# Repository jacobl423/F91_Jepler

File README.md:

# F91_Jepler

## Project Overview

The **F91_Jepler** is a complete redesign and evolution of the classic Casio F91W watch, inspired by the original [F91 Kepler](https://github.com/drpykachu/F91_Kepler) project. This project completely replaces the original internals of the watch, keeping only the original resin case and buttons, while adding an OLED display, a powerful Bluetooth-capable MCU, and a rechargeable battery system.

The redesign is in progress. Emulation, tooling and companion software are far along; the nRF52840 board itself is not fabricated, and fit and charging arrangements are not yet verified.

## Progress at a Glance

| Area | Status |
|---|---|
| **Hardware** | Original Kepler DipTrace PCBs converted to editable KiCad 10 projects; redesign draft board carried in the workbench app; BOMs and clock requirements documented. Nothing fabricated yet. |
| **Firmware** | Zephyr RTOS app boots under MCUboot in Renode: RTC-backed ticking clock, SSD1306 framebuffer over I2C, and the custom Notification and Clock GATT services ported to the Zephyr BLE stack. |
| **Emulation** | One-command firmware build with SHA-256 manifest, signed-image boot verification, browser watch viewer with real emulated framebuffer and GPIO buttons, headless boot check. |
| **Jepler Dev (macOS)** | Full Swift workbench: Renode session harness, UART terminal, watch face, firmware build/verify, automated test runner, UART test-bridge injectors, and a live KiCad suite (auto-reload viewer, 3D raytrace, DRC, Gerber export, diff). |
| **Companion app** | React + Capacitor mobile app (Android/iOS) with BLE scan/connect, GATT clock sync, mock driver and LCD watch face; **327/327 tests passing** (`npm test` in `Software/companion_app`). |

## Hardware Upgrades & Architecture

The original Kepler boards were authored in DipTrace; those files are retained unchanged in [`Hardware/PCB/`](Hardware/PCB) and have been converted into editable KiCad projects in [`Hardware/KiCad/`](Hardware/KiCad) (main board, display connector, debugger connector).

The nRF52840 redesign draft (A0) previously lived under `Hardware/KiCad/drafts/f91_jepler/`; that standalone copy was removed when the original boards were converted, and the same draft PCB now ships inside the workbench app at [`Software/macOS_App/F91JeplerEmulator/Resources/Embedded/f91_jepler.kicad_pcb`](Software/macOS_App/F91JeplerEmulator/Resources/Embedded/f91_jepler.kicad_pcb), where the Jepler Dev PCB tools open it by default. It remains an **unrouted electrical-core and placement draft, not a fabrication release**.

- **MCU:** Nordic nRF52840-QIAA, 7 × 7 mm AQFN73, with 1 MB flash and 256 KB RAM.
- **Display:** BuyDisplay ER-OLED0.83-1, a 0.83″ 96 × 39 monochrome OLED driven over I2C (SSD1306-class, Zephyr CFB framebuffer). Connector and supply details remain provisional.
- **Battery:** A small protected single-cell LiPo secured to the assembly replaces the earlier rechargeable coin-cell plan. Exact cell and fit remain provisional.
- **Power:** The draft includes a 3.0 V regulator (not a charger). Onboard charging, charge/load management and the charging connector still need design work.
- **Timekeeping:** External 32.768 kHz crystal feeding the nRF52840 RTC; see [clock circuit requirements](Hardware/CLOCKING.md).
- **Sensors:** An accelerometer and external flash remain optional; neither is in the draft.

### Bracket and charging contacts

Retain the original bracket as the mechanical reference. Its continuity, spring geometry, insulation and clearance around a new battery have not been measured. The user does not currently have it available, so those aspects remain provisional. The draft does not connect the bracket to a battery or charging net. Earlier split-cage and button-charging ideas in the historical project context are not approved electrical designs.

## Software Architecture

Moving to the nRF52840 means the original Texas Instruments SimpleLink firmware is being completely replaced. The new firmware is built on:
- **Zephyr RTOS / nRF Connect SDK:** The modern standard for Nordic BLE development.
- **MCUboot + SMP Server:** MCUboot is the first-stage bootloader with RSA-2048 signed images, and the SMP server allows safe, dual-bank Over-The-Air (OTA) Device Firmware Updates (DFU) directly from a smartphone, so the watch never needs to be opened for programming once flashed.

See [`Firmware/README.md`](Firmware/README.md) for build commands, the GATT service/characteristic map, and flashing notes.

## Development Tooling

### Jepler Dev — macOS workbench (`Software/macOS_App`)

A Swift app that combines the emulator, firmware pipeline and PCB tooling in one window:

- **Renode session harness:** launches Renode with the signed app image and matching MCUboot ELF, streams the UART console, and renders the live emulated framebuffer in a watch frame (the screen is driven by an in-repo `F91SSD1306.cs` model, not a mock drawing).
- **Firmware build & verify:** builds the Zephyr app plus its matching MCUboot image, signs it, and verifies full-file SHA-256 hashes against the generated `firmware-manifest.json` before loading anything into a session.
- **Automated tests & injectors:** boot-test runner and button-sequence presets that assert on firmware-reported state over the emulator-only UART test bridge, plus Notification/Clock service test panels (service-handler payloads, not real BLE/ATT traffic).
- **KiCad suite:** live auto-reload PCB viewer, 3D raytrace render, DRC via `kicad-cli` with SHA-256-pinned input snapshots and explicit pass / fail / inconclusive confidence, Gerber export, PCB diff and comparison, component inspector, board validation and GPIO pin audit against the compiled devicetree.

Build and launch from the repo root:

```bash
./run_emulator.sh          # builds "Jepler Dev.app" if missing, then opens it
```

### Emulation without the app (`Firmware/renode`)

```bash
bash Firmware/renode/build-display.sh   # west build + sign app & MCUboot, export manifest
bash Firmware/renode/watch-ui.sh        # watch viewer at http://127.0.0.1:8085
bash Firmware/renode/boot-check.sh      # headless MCUboot + app boot verification
```

See [`Firmware/renode/README.md`](Firmware/renode/README.md) for details, key bindings, and known limitations.

### Companion app (`Software/companion_app`)

React + Capacitor app for Android/iOS: scans for the watch by name or Clock Service UUID, connects over BLE, and syncs time / timezone / time mode / DST through the GATT clock characteristics, with a simulated-watch driver and an F-91W-style LCD for development. The suite covers serialization boundaries, the connection state machine, sync fault injection and a 4-tier E2E integration suite.

```bash
cd Software/companion_app
npm test          # Vitest: 327/327 passing
npm run typecheck && npm run build
```

## Current Project Status

- **Mechanicals:** Provisional outline and battery envelope; bracket fit unverified.
- **Schematic & PCB:** Original DipTrace boards converted to editable KiCad projects under [`Hardware/KiCad`](Hardware/KiCad); the nRF52840 redesign remains an unrouted draft (bundled with the macOS app). Original DipTrace files retained.
- **Firmware:** Zephyr, MCUboot and the ported GATT services run in Renode; see [emulation instructions](Firmware/renode/README.md). Signed-image boot and a flipped-byte rejection check pass; OTA swapping/rollback has not been tested. Simulation does not validate the physical board.
- **Software:** Jepler Dev workbench builds and launches via `run_emulator.sh`; companion app tests, typecheck and production build pass.

## Collaboration and Setup
Welcome collaborators! To get started with the repository, follow these steps:

1. **Clone the repository**:
   ```bash
   git clone <repository_url>
   cd f91_jepler
   ```

2. **Set up the Python Environment**:
   This project includes some utility scripts for parsing BOMs and STL files, and the Zephyr/west build uses the same environment. It is recommended to use a virtual environment:
   ```bash
   python3 -m venv .venv
   source .venv/bin/activate
   pip install -r requirements.txt
   ```

3. **Project Structure**:
   - `Firmware/`: Zephyr firmware source and Renode emulation tooling.
   - `Hardware/`: PCB designs (DipTrace originals and KiCad conversions), schematics, and BOMs.
   - `Software/`: Companion mobile app (`companion_app`), the Jepler Dev macOS workbench (`macOS_App`), and the legacy Android shell (`app`).

4. **Contributing**:
   - Please create a new branch for any feature or bugfix (e.g., `feature/add-new-sensor` or `bugfix/fix-display-glitch`).
   - Open a pull request against the `main` branch when your changes are ready for review.

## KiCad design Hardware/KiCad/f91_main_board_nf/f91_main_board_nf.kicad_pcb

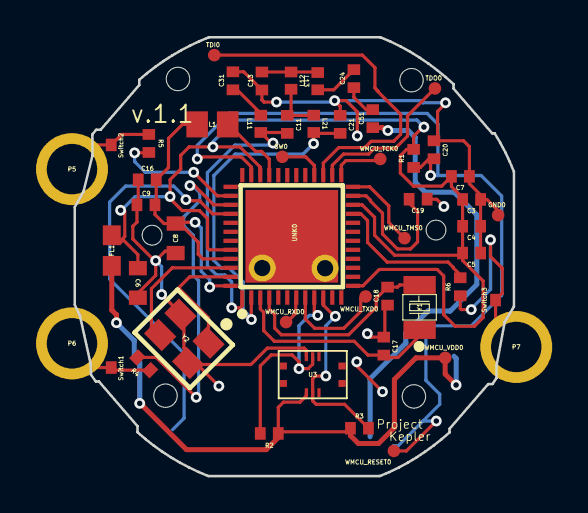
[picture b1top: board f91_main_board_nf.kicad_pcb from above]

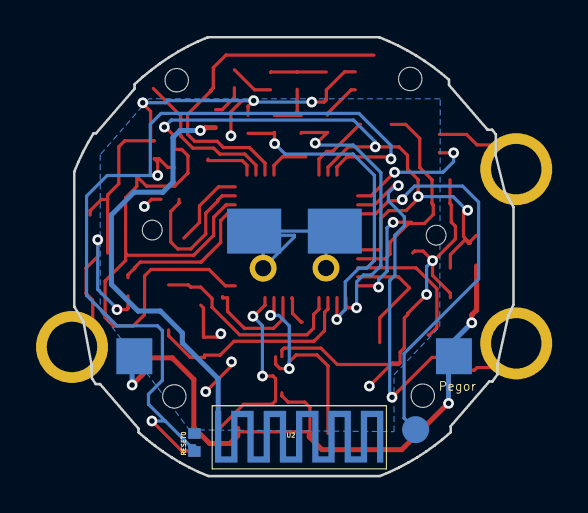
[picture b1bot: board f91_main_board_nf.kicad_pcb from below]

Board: 2 copper layers, 24.4 x 24.4 mm, 65 parts (7 on the bottom side), 35 nets.

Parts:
C3, C4, C5, C7, C9, C16, C20: 100nF; CAP_0402
C6, C8: 10uF; CAP_0603
C11, C13, C21: 1pF; CAP_0402
C17, C18, C24: 12pF; CAP_0402
C19: 1uF; CAP_0402
C31: 6.8pF; CAP_0402
C51: 1.8pF; CAP_0402
FL1: BLM18HE152SN1; CAP_0603_FL1
GND0: GND; single_probe_point
L1: 10uH; IND_0805
L11, L21: 2.4nH; IND_0402
L12, L13: 2nH; IND_0402
P5, P6, P7: CONN_01X01; PAD1
Pad1, Pad2: Pad
Pad3, Pad4: Pad; Pad_Pad3
Pad5: Pad; Pad_Pad5
Pad6, Pad7: Pad; Pad_Pad6
R1: 100k; RES_0402
R2, R3: 3.3k; RES_0402
R4, R5, R6: 100; RES_0402
RESET0: N/A DO NOT CONNECT; RES_0402_RESET
SW0: SW0; single_probe_point
Switch1, Switch2: SingleConnect
Switch3: SingleConnect; SingleConnect_Switch3
TDI0: TDI; single_probe_point
TDO0: TDO; single_probe_point
U2: BT_Antenna; BT_ANTENNA
U3: 5050660622
UNK0: CC2640(long pads); RGZ0048A-VQFN-48(longer_pads)
UNK_HOLE_0: dummyfp0
UNK_HOLE_1: dummyfp1
UNK_HOLE_2: dummyfp2
UNK_HOLE_3: dummyfp3
UNK_HOLE_4: dummyfp4
UNK_HOLE_5: dummyfp5
WMCU_RESET0: WMCU_RESET; single_probe_point_WMCU_RESET
WMCU_RXD0: WMCU_RXD; single_probe_point
WMCU_TCK0: single_probe point; single_probe_point
WMCU_TMS0: WMCU_TMS; single_probe_point
WMCU_TXD0: WMCU_TXD; single_probe_point_WMCU_TXD
WMCU_VDD0: WMCU_VDD; single_probe_point
Y1: 32.768kHz; FC-135
Y2: 24MHz; TSX-3225

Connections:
Net_0: C3.1, C4.1, C5.1, C6.1, C7.1, C8.1, C9.1, C13.1, C16.1, C17.1, C18.1, C19.1, C20.1, C21.1, C31.2, GND0.1, Pad3.1, Pad4.1, Pad6.1, Pad7.1, RESET0.1, U3.1, UNK0.49, Y2.2, Y2.4
Net_1: FL1.1, Pad1.1, Pad2.1, R2.1, R3.1, U3.4, WMCU_VDD0.1
Net_2: C3.2, C4.2, C5.2, C6.2, C7.2, FL1.2, R1.2, UNK0.13, UNK0.22, UNK0.34, UNK0.44
Net_3: L1.1, UNK0.33
Net_4: C8.2, C9.2, C16.2, L1.2, UNK0.45, UNK0.48
Net_5: UNK0.25, WMCU_TCK0.1
Net_6: UNK0.24, WMCU_TMS0.1
Net_7: C20.2, R1.1, RESET0.2, UNK0.35, WMCU_RESET0.1
Net_8: C17.2, UNK0.3, Y1.1
Net_9: C18.2, UNK0.4, Y1.2
Net_10: C19.2, UNK0.23
Net_11: UNK0.47, Y2.1
Net_12: UNK0.46, Y2.3
Net_13: C21.2, L21.2, UNK0.2
Net_14: C11.2, L11.1, UNK0.1
Net_15: C31.1, L11.2
Net_16: C11.1, L12.2, L21.1
Net_17: C13.2, L12.1, L13.2
Net_18: C24.2, L13.1
Net_19: C24.1, C51.2
Net_20: C51.1, U2.1, U2.1_1, U2.1_2, U2.1_3, U2.1_4, U2.1_5, U2.1_6, U2.1_7, U2.1_8, U2.1_9, U2.1_10, U2.1_11, U2.1_12, U2.1_13, U2.1_14, U2.1_15, U2.1_16, U2.1_17, U2.1_18, U2.1_19, U2.1_20
Net_21: UNK0.7, WMCU_RXD0.1
Net_22: UNK0.8, WMCU_TXD0.1
Net_23: TDO0.1, UNK0.26
Net_24: TDI0.1, UNK0.27
Net_25: SW0.1, UNK0.28
Net_26: Pad5.1, UNK0.40
Net_30: R3.2, U3.5, UNK0.10
Net_31: R2.2, U3.2, UNK0.9
Net_32: R6.2, UNK0.21
Net_33: R5.2, UNK0.38
Net_34: R4.2, UNK0.39
Net_35: P6.1, R4.1, Switch1.1
Net_36: P5.1, R5.1, Switch2.1
Net_37: P7.1, R6.1, Switch3.1

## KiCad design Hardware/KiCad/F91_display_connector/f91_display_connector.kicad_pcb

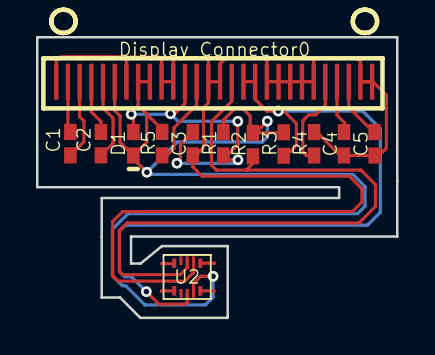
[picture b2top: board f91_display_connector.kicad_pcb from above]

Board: 2 copper layers, 20.0 x 15.6 mm, 13 parts (0 on the bottom side), 14 nets.

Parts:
C1, C2: 1uF; CAP_0402
C3: 10uF; CAP_0402_C3
C4, C5: 4.7uF; CAP_0402_C3
D1: DIODE_0402; DIO_0402
Display_Connector0: 0.83-OLED_28Pin; 0.83-OLED_28pin
R1, R2, R3: 10k; RES_0402
R4: 390k; RES_0402
R5: 4.7k; RES_0402
U2: 5050700622

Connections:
Net_0: C3.1, C4.1, C5.1, Display_Connector0.1, Display_Connector0.7, Display_Connector0.10, Display_Connector0.11, Display_Connector0.14, Display_Connector0.15, Display_Connector0.19, Display_Connector0.20, Display_Connector0.21, Display_Connector0.22, Display_Connector0.23, Display_Connector0.27, Display_Connector0.28, R4.2, U2.1
Net_1: C1.1, Display_Connector0.2
Net_2: C1.2, Display_Connector0.3
Net_3: C2.1, Display_Connector0.4
Net_4: C2.2, Display_Connector0.5
Net_5: D1.1, Display_Connector0.6, Display_Connector0.8, Display_Connector0.9, R1.2, R2.2, R3.2, R5.2, U2.4
Net_6: C3.2, D1.2, Display_Connector0.12, R1.1
Net_7: Display_Connector0.16, R2.1, U2.2
Net_8: Display_Connector0.17, Display_Connector0.18, R3.1, U2.5
Net_9: Display_Connector0.24, R4.1
Net_10: C4.2, Display_Connector0.25
Net_11: C5.2, Display_Connector0.26
Net_12: U2.0@, U2.0@_1, U2.0@_2, U2.0@_3
Net_13: Display_Connector0.13, R5.1

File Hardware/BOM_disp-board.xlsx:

Name | Value | Manufacturer | Quantity | Pattern | Link
CAP_0402 | 1uF |  | 2 | CAP_0402
CAP_0402 | 10uF |  | 1 | CAP_0402
CAP_0402 | 4.7uF |  | 2 | CAP_0402
DIODE_0402 |  |  | 1 | DIO_0402
RES_0402 | 10k |  | 3 | RES_0402
RES_0402 | 390k |  | 1 | RES_0402
RES_0402 | 4.7k |  | 1 | RES_0402
Board to Board & Mezzanine |  | Molex | 1 | 5050700622 | https://www.mouser.com/ProductDetail/538-505070-0622
0.83" OLED Display (White, for Green Gel) |  |  | 1 |  | https://www.buydisplay.com/0-83-inch-oled-display-module-spi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

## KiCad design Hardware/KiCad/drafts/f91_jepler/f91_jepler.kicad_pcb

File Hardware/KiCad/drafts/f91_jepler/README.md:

# F91 Jepler — KiCad A0 draft

Open `f91_jepler.kicad_pro` in KiCad 10. The schematic and PCB are editable.
This is an **unrouted electrical-core and placement draft, not a complete watch
board or a fabrication release**. The original DipTrace files are unchanged.

## Captured circuitry

- nRF52840-QIAA, Nordic AQFN73, based on Nordic reference configuration 6:
  normal VDD supply, internal LDO, no USB. VDDH joins VDD; VBUS joins ground.
  Firmware must disable the MCU DC/DC converters for this circuit.
- 32 MHz crystal circuit with reference load capacitors. Exact crystal MPN
  and loading remain to be selected; the footprint is provisional.
- ABS07-32.768KHZ-7-T between XL1/XL2, with provisional 9 pF load capacitors.
  See [clock requirements](../../../CLOCKING.md). PCB parasitics require verification.
- TPS78230DDC 3.0 V regulator, input/output capacitors, and pads for a protected
  single-cell LiPo's factory-fitted leads. This regulator is **not** a charger
  or battery protection circuit. Do not solder directly to a bare pouch cell.
- SWD, reset, and power pads; reference RF matching network with a test pad,
  **no antenna**; provisional I2C display signal pads, **no OLED connector**.
- C10, C13 and C22 are unpopulated reference options. C9's 820 pF is for older
  MCU revisions; Nordic says it is unnecessary for build code Fxx and later.

## Buttons and bracket

| Position | Button/key | Proposed GPIO | Pad |
|---|---|---|---|
| Top left | A / 1 | P0.11 | TP3 |
| Bottom left | B / 2 | P0.12 | TP4 |
| Bottom right | C / 3 | P0.24 | TP5 |

These match the existing emulator assignments, **not a verified physical PCB**.
The proposal uses active-low inputs with firmware pull-ups. TP16 is a proposed
ground return for discrete switches. It does not establish that the original
bracket is grounded or that the existing spring contacts are compatible.
No footprint or copper connection represents the actual bracket. Charging
contacts are not assigned to the button contacts or bracket.

The user does not have the bracket available for measurement. Its continuity,
spring geometry, retention points, and battery clearance remain provisional.
Do not cut or electrically modify it on the basis of this draft.

## Mechanical assumptions

The 24 × 23.5 mm chamfered outline and 0.8 mm PCB thickness are planning
assumptions. They were **not** recovered from the DipTrace board or validated
against a case. The movement-holder mesh has an outer bounding box of about
26.18 × 25.47 × 4.40 mm; this is not the usable PCB or battery cavity.

The drawing-layer rectangle is a **16 × 12 mm rear battery space study**.
It is not a selected battery, copper keepout, or proof of fit. Battery thickness,
protection circuit, wires, insulation, swelling allowance, mounting adhesive,
and clearance from the metal bracket all still need a mechanical stack-up.
No mounting holes or bracket slots have been invented.

## Work required before a prototype order

1. Establish the actual case/holder cavity and bracket connections, then replace
   the provisional outline, contact pads, and battery envelope with measured geometry.
2. Select the protected LiPo and its permitted charge current and temperature
   limits. Capture the BQ25100 charger, temperature sensing, ESD/input protection,
   charging connector and system-load isolation or power path. These are **not
   implemented**. BQ25100 alone does not supply a complete power path; system
   load can affect charge termination. There is no working charging input yet.
3. Resolve the display connections: the firmware currently uses I2C (`i2c0` at `0x3c`), which matches the legacy Kepler hardware. The OLED module must be ordered as the I2C variant or modified (BS0/BS1 resistors) for I2C. Verify the exact supply rails, reset, pinout, FPC land pattern and pull-ups before wiring it.
4. Select the RF antenna and design its keepout/matching for the actual case,
   battery and metal bracket. The RF test pad is not a working antenna.
5. Complete the four-layer stack-up and copper routing. This draft has no
   tracks, vias or ground pours. Decoupling, RF return paths and crystal layout
   must be designed together. Confirm the board house can assemble AQFN73.
6. Select final passive ratings and crystal part numbers; review firmware power
   configuration, battery-voltage monitoring and low-battery behavior. Then run
   full ERC/DRC and hardware bring-up. Passing ERC alone does not validate a circuit.

`components.csv` is an inventory of the draft, not a purchasing BOM. Test pads
are copper features, not separate parts. Optional accelerometer and external
flash are not included in A0.

## References and verification

- [Nordic official QIAA reference layout v1.3](https://nsscprodmedia.blob.core.windows.net/prod/software-and-other-downloads/reference-layouts/nrf52840/nrf52840-qiaa-reference-layout-1_3.zip),
  configuration 6 schematic. The reference PCB was imported only for reading
  its component/net assignments; its routing is **not** reused in this draft.
- [TI TPS782 datasheet](https://www.ti.com/lit/ds/symlink/tps782.pdf).
- [TI BQ25100 datasheet](https://www.ti.com/lit/ds/symlink/bq25100.pdf),
  for the pending charging design.
- Standard KiCad 10 symbols and footprints are embedded in the design files.

Review outputs and manufacturer downloads live under `build/hardware-reference/`
inside this repository. See `VALIDATION.md` for the recorded check results.

`tools/create_draft.py` generated this initial version using KiCad's bundled
Python and standard libraries. It requires the Nordic config6 PCB imported at
`build/hardware-reference/nordic-config6.kicad_pcb`. **Do not rerun it after
editing the design**: it overwrites the schematic, PCB, project and inventory.
Future design work should edit the native KiCad files.

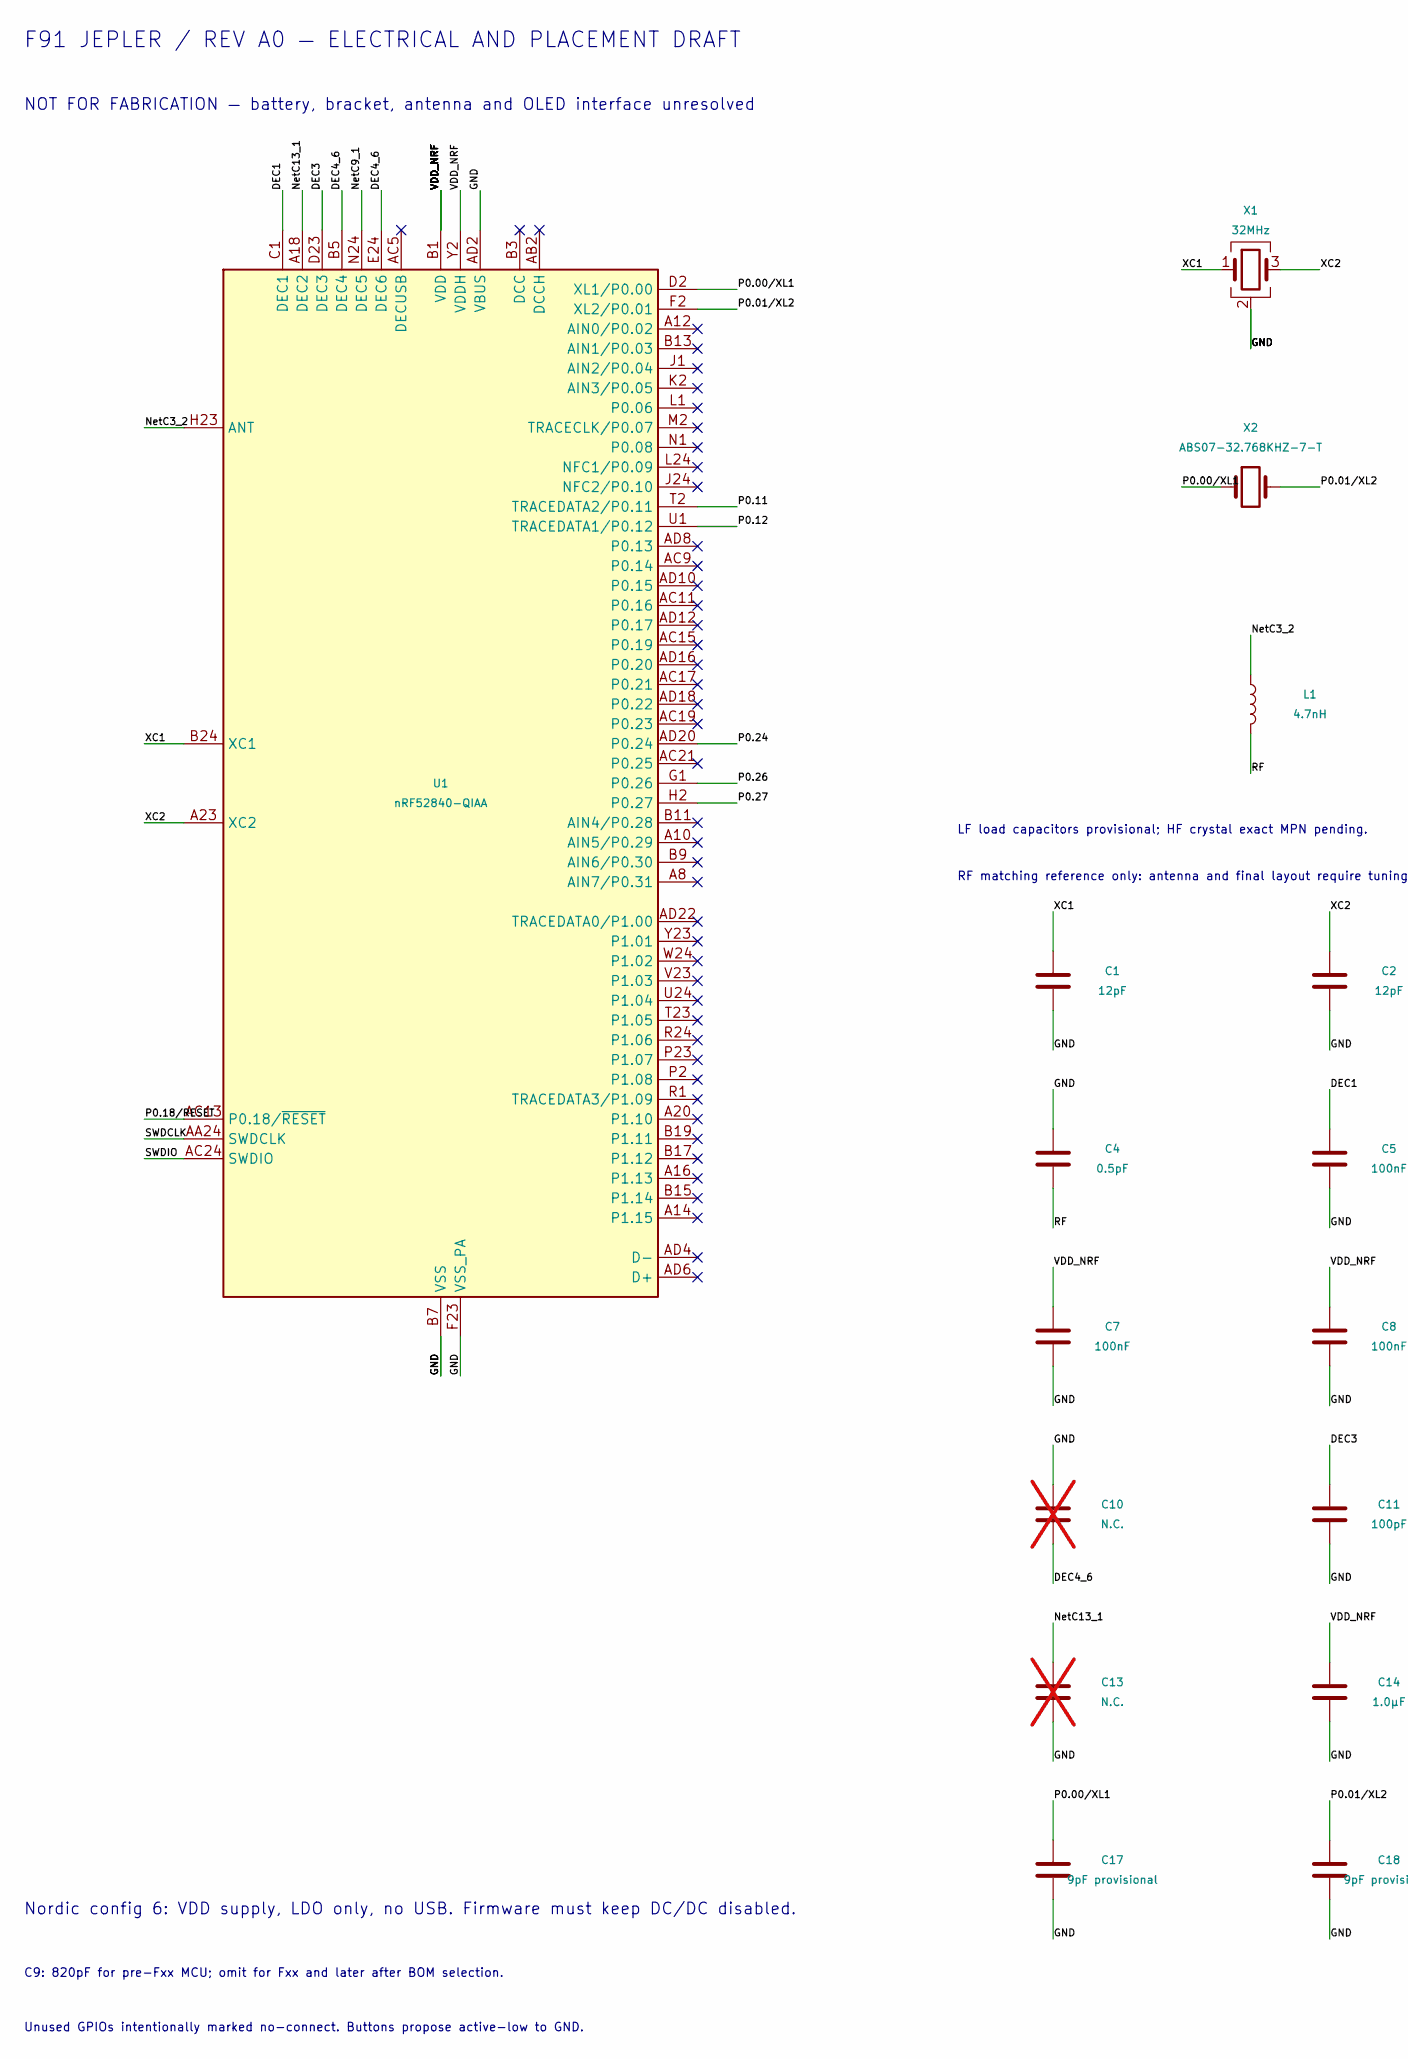
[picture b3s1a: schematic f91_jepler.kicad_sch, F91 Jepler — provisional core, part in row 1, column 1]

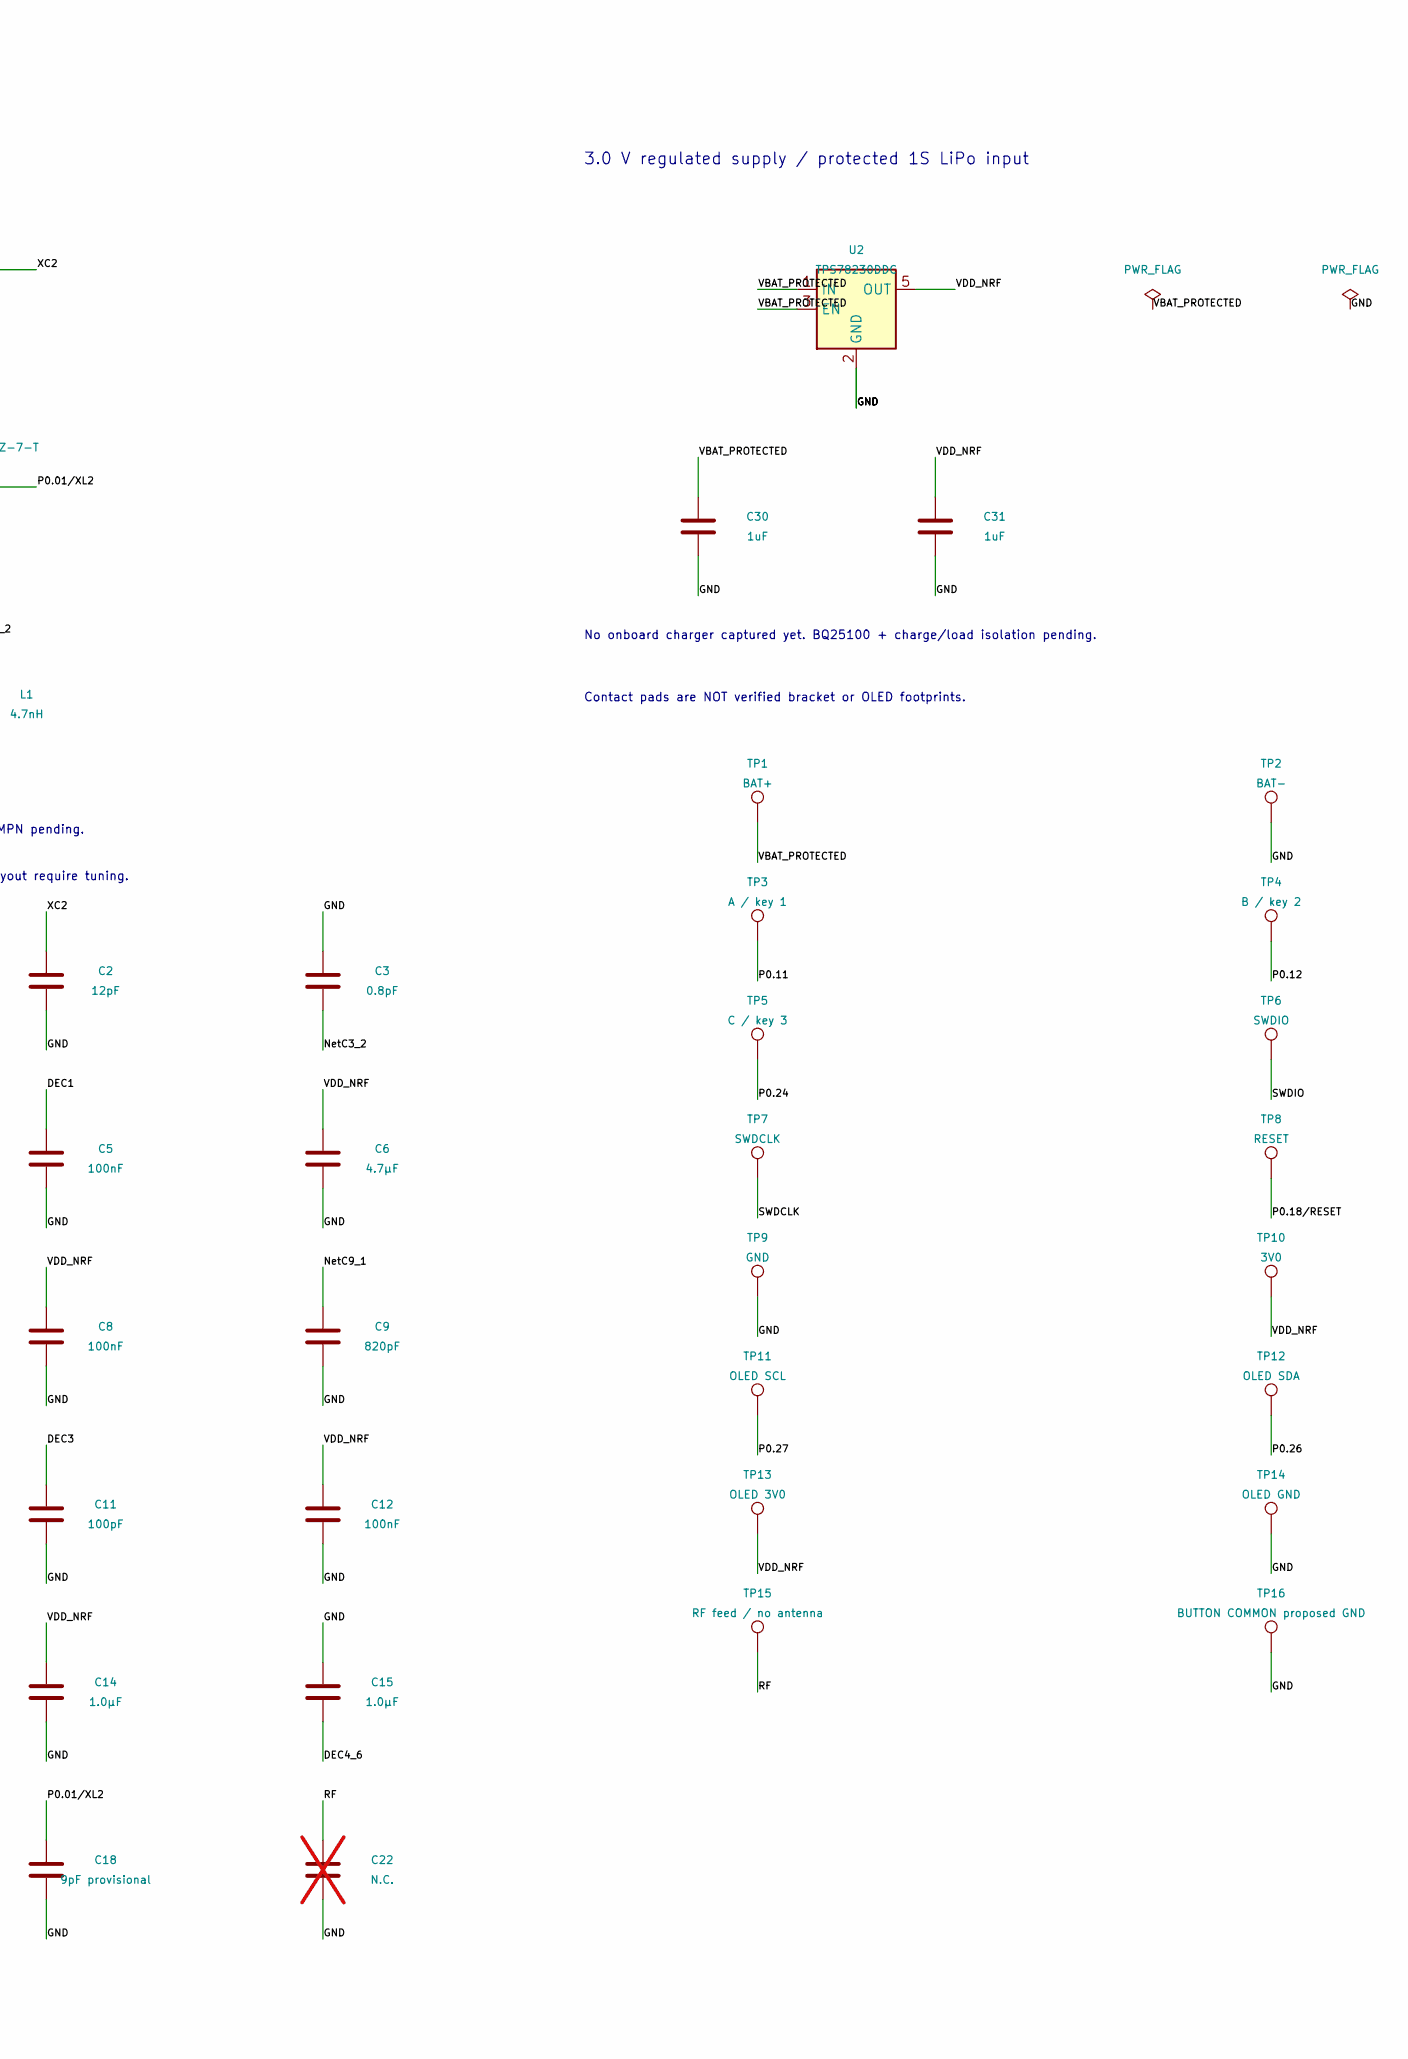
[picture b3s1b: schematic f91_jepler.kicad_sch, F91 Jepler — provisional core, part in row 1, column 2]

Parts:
C1, C2: 12pF; C_0402_1005Metric
C3: 0.8pF; C_0402_1005Metric
C4: 0.5pF; C_0402_1005Metric
C5, C7, C8, C12: 100nF; C_0402_1005Metric
C6: 4.7µF; C_0402_1005Metric
C9: 820pF; C_0402_1005Metric
C10, C13, C22: N.C.; C_0402_1005Metric; not fitted
C11: 100pF; C_0402_1005Metric
C14, C15: 1.0µF; C_0402_1005Metric
C17, C18: 9pF provisional; C_0402_1005Metric
C30, C31: 1uF; C_0402_1005Metric
L1: 4.7nH; L_0402_1005Metric
TP1: BAT+; TestPoint_Pad_D1.0mm
TP2: BAT-; TestPoint_Pad_D1.0mm
TP3: A / key 1; TestPoint_Pad_D1.0mm
TP4: B / key 2; TestPoint_Pad_D1.0mm
TP5: C / key 3; TestPoint_Pad_D1.0mm
TP6: SWDIO; TestPoint_Pad_D1.0mm
TP7: SWDCLK; TestPoint_Pad_D1.0mm
TP8: RESET; TestPoint_Pad_D1.0mm
TP9: GND; TestPoint_Pad_D1.0mm
TP10: 3V0; TestPoint_Pad_D1.0mm
TP11: OLED SCL; TestPoint_Pad_D1.0mm
TP12: OLED SDA; TestPoint_Pad_D1.0mm
TP13: OLED 3V0; TestPoint_Pad_D1.0mm
TP14: OLED GND; TestPoint_Pad_D1.0mm
TP15: RF feed / no antenna; TestPoint_Pad_D1.0mm
TP16: BUTTON COMMON proposed GND; TestPoint_Pad_D1.0mm
U1: nRF52840-QIAA; Nordic_AQFN-73-1EP_7x7mm_P0.5mm
U2: TPS78230DDC; TSOT-23-5
X1: 32MHz; Crystal_SMD_2016-4Pin_2.0x1.6mm
X2: ABS07-32.768KHZ-7-T; Crystal_SMD_3215-2Pin_3.2x1.5mm

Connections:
/DEC1: C5.1, U1.C1 (DEC1)
/DEC3: C11.1, U1.D23 (DEC3)
/DEC4_6: C10.2, C15.2, U1.B5 (DEC4), U1.E24 (DEC6)
/GND: C1.2, C2.2, C3.1, C4.1, C5.2, C6.2, C7.2, C8.2, C9.2, C10.1, C11.2, C12.2, C13.2, C14.2, C15.1, C17.2, C18.2, C22.2, C30.2, C31.2, TP2.1, TP9.1, TP14.1, TP16.1, U1.AD2 (VBUS), U1.B7 (VSS), U1.EP (VSS), U1.F23 (VSS_PA), U2.2 (GND), U2.4 (GND), X1.2 (G), X1.4 (G)
/NetC3_2: C3.2, L1.1, U1.H23 (ANT)
/NetC9_1: C9.1, U1.N24 (DEC5)
/NetC13_1: C13.1, U1.A18 (DEC2)
/P0.00/XL1: C17.1, U1.D2 (XL1/P0.00), X2.1
/P0.01/XL2: C18.1, U1.F2 (XL2/P0.01), X2.2
/P0.11: TP3.1, U1.T2 (TRACEDATA2/P0.11)
/P0.12: TP4.1, U1.U1 (TRACEDATA1/P0.12)
/P0.18/RESET: TP8.1, U1.AC13 (P0.18/~RESET)
/P0.24: TP5.1, U1.AD20 (P0.24)
/P0.26: TP12.1, U1.G1 (P0.26)
/P0.27: TP11.1, U1.H2 (P0.27)
/RF: C4.2, C22.1, L1.2, TP15.1
/SWDCLK: TP7.1, U1.AA24 (SWDCLK)
/SWDIO: TP6.1, U1.AC24 (SWDIO)
/VBAT_PROTECTED: C30.1, TP1.1, U2.1 (IN), U2.3 (EN)
/VDD_NRF: C6.1, C7.1, C8.1, C12.1, C14.1, C31.1, TP10.1, TP13.1, U1.A22 (VDD), U1.AD14 (VDD), U1.AD23 (VDD), U1.B1 (VDD), U1.W1 (VDD), U1.Y2 (VDDH), U2.5 (OUT)
/XC1: C1.1, U1.B24 (XC1), X1.1
/XC2: C2.1, U1.A23 (XC2), X1.3

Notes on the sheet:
F91 JEPLER / REV A0 — ELECTRICAL AND PLACEMENT DRAFT
NOT FOR FABRICATION — battery, bracket, antenna and OLED interface unresolved
Nordic config 6: VDD supply, LDO only, no USB. Firmware must keep DC/DC disabled.
3.0 V regulated supply / protected 1S LiPo input
No onboard charger captured yet. BQ25100 + charge/load isolation pending.
Contact pads are NOT verified bracket or OLED footprints.
LF load capacitors provisional; HF crystal exact MPN pending.
RF matching reference only: antenna and final layout require tuning.
C9: 820pF for pre-Fxx MCU; omit for Fxx and later after BOM selection.
Unused GPIOs intentionally marked no-connect. Buttons propose active-low to GND.

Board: 4 copper layers, 41 parts (0 on the bottom side), 22 nets, no tracks yet.

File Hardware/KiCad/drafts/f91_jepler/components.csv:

Reference,Value,Footprint,DNP,Status
C7,100nF,Capacitor_SMD:C_0402_1005Metric,False,DRAFT - not purchasing BOM
C18,9pF provisional,Capacitor_SMD:C_0402_1005Metric,False,DRAFT - not purchasing BOM
C13,N.C.,Capacitor_SMD:C_0402_1005Metric,True,DRAFT - not purchasing BOM
C4,0.5pF,Capacitor_SMD:C_0402_1005Metric,False,DRAFT - not purchasing BOM
C3,0.8pF,Capacitor_SMD:C_0402_1005Metric,False,DRAFT - not purchasing BOM
C15,1.0µF,Capacitor_SMD:C_0402_1005Metric,False,DRAFT - not purchasing BOM
C9,820pF,Capacitor_SMD:C_0402_1005Metric,False,DRAFT - not purchasing BOM
C1,12pF,Capacitor_SMD:C_0402_1005Metric,False,DRAFT - not purchasing BOM
U1,nRF52840-QIAA,Package_DFN_QFN:Nordic_AQFN-73-1EP_7x7mm_P0.5mm,False,DRAFT - not purchasing BOM
X1,32MHz,Crystal:Crystal_SMD_2016-4Pin_2.0x1.6mm,False,DRAFT - not purchasing BOM
X2,ABS07-32.768KHZ-7-T,Crystal:Crystal_SMD_3215-2Pin_3.2x1.5mm,False,DRAFT - not purchasing BOM
C11,100pF,Capacitor_SMD:C_0402_1005Metric,False,DRAFT - not purchasing BOM
C17,9pF provisional,Capacitor_SMD:C_0402_1005Metric,False,DRAFT - not purchasing BOM
C6,4.7µF,Capacitor_SMD:C_0402_1005Metric,False,DRAFT - not purchasing BOM
C5,100nF,Capacitor_SMD:C_0402_1005Metric,False,DRAFT - not purchasing BOM
C2,12pF,Capacitor_SMD:C_0402_1005Metric,False,DRAFT - not purchasing BOM
C10,N.C.,Capacitor_SMD:C_0402_1005Metric,True,DRAFT - not purchasing BOM
C12,100nF,Capacitor_SMD:C_0402_1005Metric,False,DRAFT - not purchasing BOM
C14,1.0µF,Capacitor_SMD:C_0402_1005Metric,False,DRAFT - not purchasing BOM
C8,100nF,Capacitor_SMD:C_0402_1005Metric,False,DRAFT - not purchasing BOM
L1,4.7nH,Inductor_SMD:L_0402_1005Metric,False,DRAFT - not purchasing BOM
C22,N.C.,Capacitor_SMD:C_0402_1005Metric,True,DRAFT - not purchasing BOM
U2,TPS78230DDC,Package_TO_SOT_SMD:TSOT-23-5,False,DRAFT - not purchasing BOM
C30,1uF,Capacitor_SMD:C_0402_1005Metric,False,DRAFT - not purchasing BOM
C31,1uF,Capacitor_SMD:C_0402_1005Metric,False,DRAFT - not purchasing BOM
TP1,BAT+,TestPoint:TestPoint_Pad_D1.0mm,False,DRAFT - not purchasing BOM
TP2,BAT-,TestPoint:TestPoint_Pad_D1.0mm,False,DRAFT - not purchasing BOM
TP3,A / key 1,TestPoint:TestPoint_Pad_D1.0mm,False,DRAFT - not purchasing BOM
TP4,B / key 2,TestPoint:TestPoint_Pad_D1.0mm,False,DRAFT - not purchasing BOM
TP5,C / key 3,TestPoint:TestPoint_Pad_D1.0mm,False,DRAFT - not purchasing BOM
TP6,SWDIO,TestPoint:TestPoint_Pad_D1.0mm,False,DRAFT - not purchasing BOM
TP7,SWDCLK,TestPoint:TestPoint_Pad_D1.0mm,False,DRAFT - not purchasing BOM
TP8,RESET,TestPoint:TestPoint_Pad_D1.0mm,False,DRAFT - not purchasing BOM
TP9,GND,TestPoint:TestPoint_Pad_D1.0mm,False,DRAFT - not purchasing BOM
TP10,3V0,TestPoint:TestPoint_Pad_D1.0mm,False,DRAFT - not purchasing BOM
TP11,OLED SCL,TestPoint:TestPoint_Pad_D1.0mm,False,DRAFT - not purchasing BOM
TP12,OLED SDA,TestPoint:TestPoint_Pad_D1.0mm,False,DRAFT - not purchasing BOM
TP13,OLED 3V0,TestPoint:TestPoint_Pad_D1.0mm,False,DRAFT - not purchasing BOM
TP14,OLED GND,TestPoint:TestPoint_Pad_D1.0mm,False,DRAFT - not purchasing BOM
TP15,RF feed / no antenna,TestPoint:TestPoint_Pad_D1.0mm,False,DRAFT - not purchasing BOM
TP16,BUTTON COMMON proposed GND,TestPoint:TestPoint_Pad_D1.0mm,False,DRAFT - not purchasing BOM

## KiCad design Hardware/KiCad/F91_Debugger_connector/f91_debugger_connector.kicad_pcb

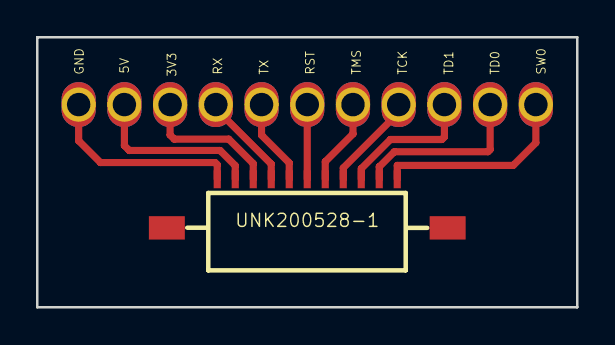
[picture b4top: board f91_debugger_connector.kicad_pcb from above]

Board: 2 copper layers, 30.0 x 15.0 mm, 12 parts (0 on the bottom side), 11 nets.

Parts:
Pad1, Pad2, Pad3, Pad4, Pad5, Pad6, Pad7, Pad8, Pad9, Pad10, Pad11: Pad; 51022-0500
UNK200528-1: Debugger; 11_FPC_MOLEX

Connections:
Net_0: Pad1.1, UNK200528-1.1
Net_1: Pad2.1, UNK200528-1.2
Net_2: Pad3.1, UNK200528-1.3
Net_3: Pad4.1, UNK200528-1.4
Net_4: Pad5.1, UNK200528-1.5
Net_5: Pad6.1, UNK200528-1.6
Net_6: Pad7.1, UNK200528-1.7
Net_7: Pad8.1, UNK200528-1.8
Net_8: Pad9.1, UNK200528-1.9
Net_9: Pad10.1, UNK200528-1.10
Net_10: Pad11.1, UNK200528-1.11
